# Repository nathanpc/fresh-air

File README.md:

# Fresh Air

The project used for [Nathan Campos](https://nathancampos.me/)'s video mapping
semester that was adapted to give a workshop on how to properly setup a Unity
interactive animation to work with a multi-layered video mapping projection.

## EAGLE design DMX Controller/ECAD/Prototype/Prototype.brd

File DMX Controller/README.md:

# MintyDMX

A tiny DMX controller that fits neatly inside an Altoids tin.

## License

<br />This work is licensed under a <a rel="license" href="http://creativecommons.org/licenses/by-nc-sa/4.0/">Creative Commons Attribution-NonCommercial-ShareAlike 4.0 International License</a>.

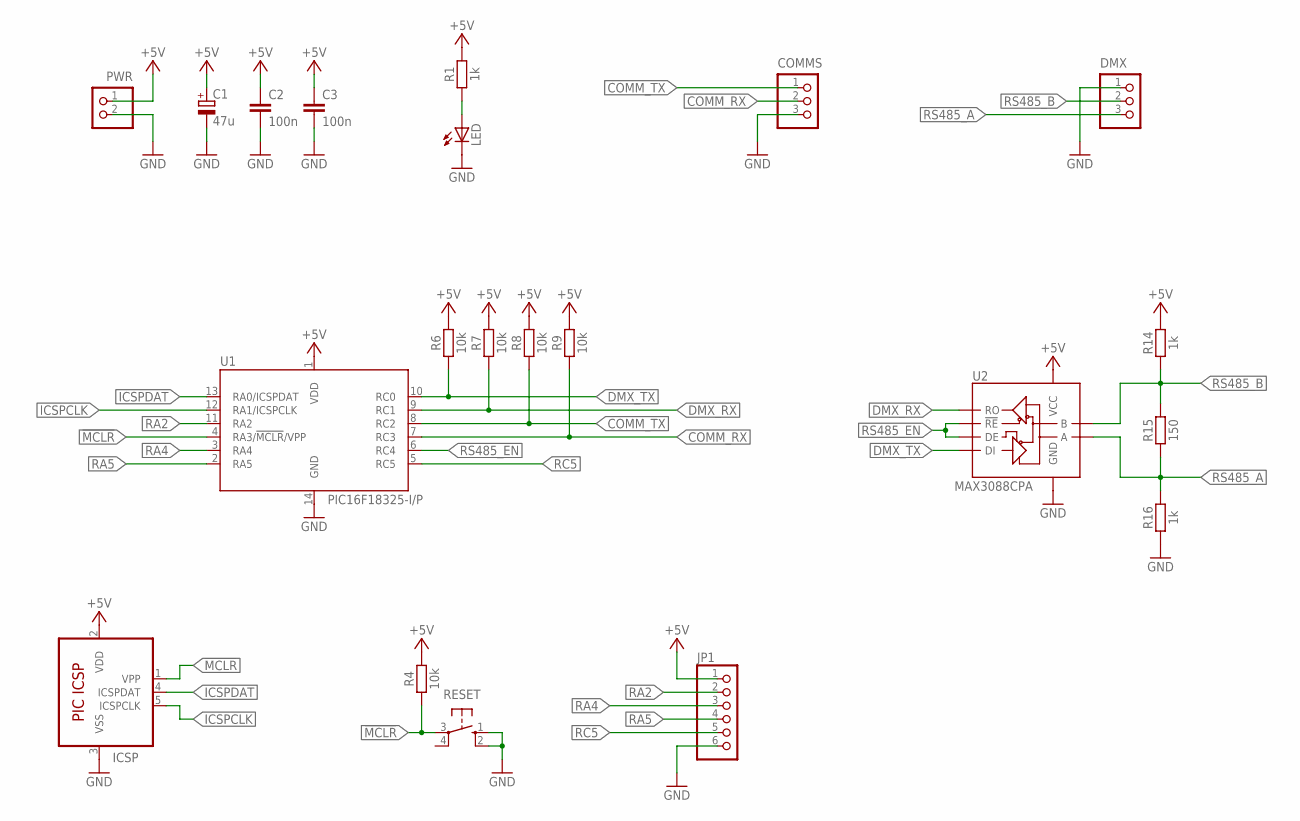
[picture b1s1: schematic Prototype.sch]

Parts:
C1: 47u; E2,5-6
C2, C3: 100n; C050-025X075
COMMS: B3B-XH-A
DMX: B3B-XH-A
ICSP: PIC-ICSP-XH6; B6B-XH-A
JP1: PINHD-1X6; 1X06
LED: LED-JST-XH; B2B-XH-A
PWR: B2B-XH-A
R1, R14, R16: 1k; 0207/10
R4, R6, R7, R8, R9: 10k; 0207/10
R15: 150; 0207/10
RESET: TACT-4PIN-THT; B3F-10XX
U1: PIC16F18325-I/P; DIL14
U2: MAX3088CPA; DIP-8

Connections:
!MCLR: ICSP.1 (VPP), R4.1, RESET.3, U1.4 (RA3/!MCLR!/VPP)
+5V: C1.+, C2.1, C3.1, ICSP.2 (VDD), JP1.1, PWR.1, R1.2, R4.2, R6.2, R7.2, R8.2, R9.2, R14.2, U1.1 (VDD), U2.8 (VCC)
COMM_RX: COMMS.2, R9.1, U1.7 (RC3)
COMM_TX: COMMS.1, R8.1, U1.8 (RC2)
DMX_RX: R7.1, U1.9 (RC1), U2.1 (RO)
DMX_TX: R6.1, U1.10 (RC0), U2.4 (DI)
GND: C1.-, C2.2, C3.2, COMMS.3, DMX.1, ICSP.3 (VSS), JP1.6, LED.2 (C), PWR.2, R16.1, RESET.1 (S), RESET.2 (S1), U1.14 (GND), U2.5 (GND)
ICSPCLK: ICSP.5 (ICSPCLK), U1.12 (RA1/ICSPCLK)
ICSPDAT: ICSP.4 (ICSPDAT), U1.13 (RA0/ICSPDAT)
unnamed: LED.1 (A), R1.1
RA2: JP1.2, U1.11 (RA2)
RA4: JP1.3, U1.3 (RA4)
RA5: JP1.4, U1.2 (RA5)
RC5: JP1.5, U1.5 (RC5)
RS485_A: DMX.3, R15.1, R16.2, U2.6 (A)
RS485_B: DMX.2, R14.1, R15.2, U2.7 (B)
RS485_EN: U1.6 (RC4), U2.2 (!RE), U2.3 (DE)

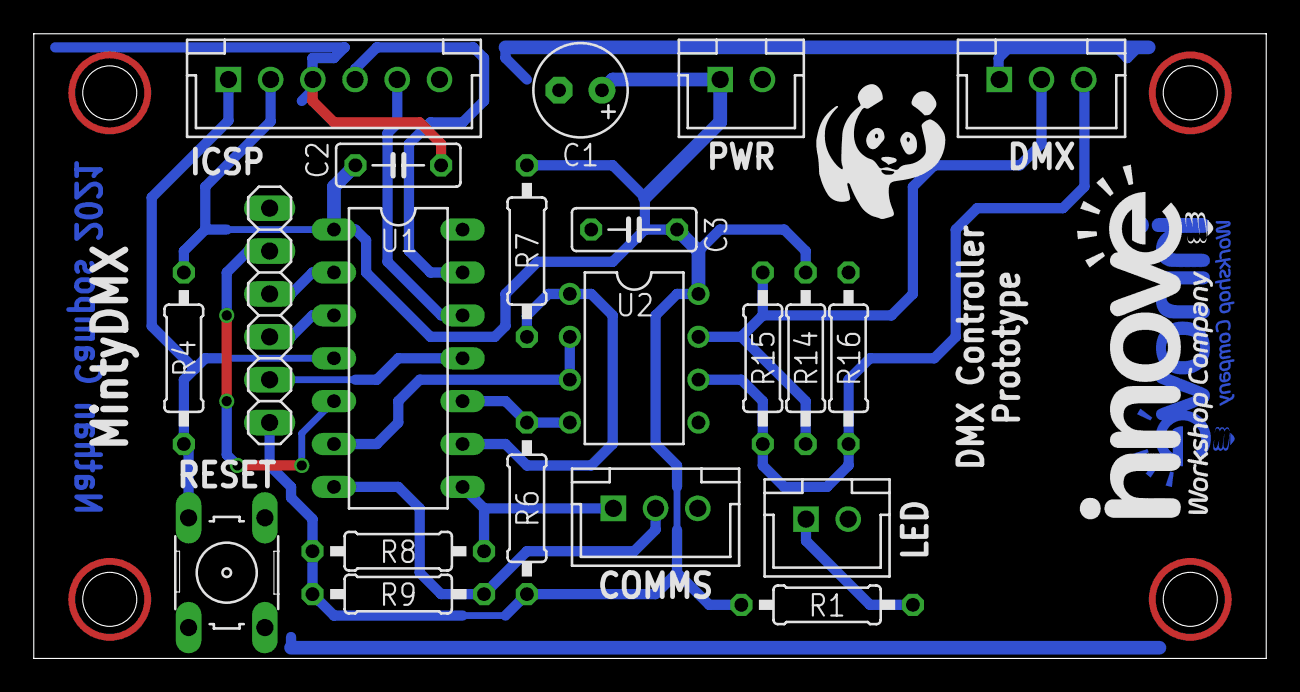
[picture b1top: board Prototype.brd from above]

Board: 2 copper layers, 73.0 x 37.0 mm, 21 parts (0 on the bottom side), 17 nets.

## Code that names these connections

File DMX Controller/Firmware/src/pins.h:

/* 
 * pins.h
 * Pin definitions.
 * 
 * @author Nathan Campos <nathan@innoveworkshop.com>
 */

#ifndef PINS_H
#define	PINS_H

//               16F18325
//             +----------+
// ICSP Data  -|RA0    RC0|- DMX Transmitter
// ICSP Clock -|RA1    RC1|- DMX Receiver
// Aux 1      -|RA2    RC2|- UART Transmitter
// Reset      -|RA3    RC3|- UART Receiver
// Aux 2      -|RA4    RC4|- DMX TX Enable
// Aux 3      -|RA5    RC5|- Aux 4
//             +----------+


// Pin definitions.
#define AUX_1     (1 << 2)  // RA2
#define AUX_2     (1 << 4)  // RA4
#define AUX_3     (1 << 5)  // RA5
#define DMX_TX    1         // RC0
#define DMX_RX    (1 << 1)  // RC1
#define UART_TX   (1 << 2)  // RC2
#define UART_RX   (1 << 3)  // RC3
#define DMX_TX_EN (1 << 4)  // RC4
#define AUX_4     (1 << 5)  // RC5

#endif	/* PINS_H */

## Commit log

2021-04-20 Empty Unity project
2021-04-29 Added paid scenary models
2021-04-29 inicial changes
2021-04-30 Basis for path following
2021-04-30 Movement proof-of-concept done
2021-04-30 Organized the code of the PathFollower script
2021-04-30 Modified the PathFollower script so that it's attached to characters instead of a waypoint container
2021-05-02 LMHPOLY assets
2021-05-02 Terrain
2021-05-02 terrain color
2021-05-02 rocks
2021-05-10 Removed the SampleScene
2021-05-10 Played around with a giant ball to simulate the fog effect
2021-05-10 Created all of the basic scripts to handle the movement interaction
2021-05-10 Tested the simple keyboard interaction using the keybaord
2021-05-10 Added support for an object to be controlled from the microphone hub adapter
2021-05-13 Improved the serial buffer parsing
2021-05-13 Joined the path follower with the microphone controller tests
2021-05-13 Added the ability to restart the path following
2021-05-24 missing color / sky
2021-05-24 scenary
2021-05-24 Added a way for the path follower script to stop for a while at some point
2021-05-24 Organized the scripts
2021-05-24 Started working on the prototype scene
2021-05-24 Enabled waypoints to change the object's rotation
2021-05-24 Added the fog to the prototype scene
2021-05-25 Fixed a variable name in WaypointStop
2021-05-25 Added scripts to handle the transformations
2021-05-25 Playing around with transformations
2021-05-25 Removed the unused collider script
2021-05-25 Added a simple function to debug unassigned references in the Inspector
2021-05-25 Added the ability for a waypoint to make the character jump
2021-05-26 2nd del scenary
2021-05-26 Imported the terrain changes and organized the scene
2021-05-26 Moved the terrain development scene
2021-05-26 Organized the project directory
2021-05-26 Put all of the characters in the scene and defined all of their waypoints
2021-05-26 Moving the fog after its animation has finished
2021-05-26 Fixed the transformation radius problems
2021-05-26 Added the ability to speed up and slow down the whole animation
2021-05-26 Finished all of the camera positions
2021-05-26 Added a script to change the material of a tree
2021-05-26 Changing the materials of Tree05
2021-05-26 Created and organized the tree materials
2021-05-26 Set all of the transform materials for the trees
2021-05-26 Populated the isolated terrain a bit
2021-05-26 Added the Main Scene to the build settings
2021-05-27 Minor change to the way the microphone controller is polled
2021-05-27 Added the Arduino source code that I forgot to put in
2021-06-21 new scenary
2021-06-23 Added Design students models
2021-06-23 Improved the interaction scripts just a bit
2021-06-23 Created the basis for the DMX stuff
2021-06-23 Organized all of the serial port scripts into their own folder
2021-06-23 Created a simple class just to provide baud rates to make it easier for people to use the DMX library
2021-06-23 Finished implementing the DMX spotlight
2021-06-23 Fully implemented the DMX robot light
2021-06-25 scenary & characters
2021-06-25 Implemented the fog machine interaction
2021-06-25 Improved the serial communication
2021-06-25 Started working on mapping things
2021-06-26 Implemented the new waypoint system and integrated animations
2021-06-26 Renamed the script testing scene
2021-06-26 Added the new scenery back
2021-06-26 Fixed the animations and waypoints
2021-06-26 Organized the workspace
2021-06-26 Organized everything and prepared the scene for waypoints
2021-06-27 Fixed the rotation of characters when using the waypoint rotation
2021-06-27 ccameras & waypoints
    camera waypoints fix:
    +- 2x entre o 1 waypoint e o 6
    rotaçao mais lenta entre waypoint 5 e 6
    segurar a camera no waypoint 6
2021-06-27 Implemented the fog shader
2021-06-27 Renamed the old scene
2021-06-27 Built a shader to transform textures
2021-06-27 Added a script to control the transformation shader
2021-06-27 Added a way to control the speed of movement between waypoints and fixed some of the waypoints
2021-06-30 Finished the project way late at night (6am) so here's huge dump of all the changes
2021-10-14 Stuff that was changed for the recording last semester
2022-06-05 Removed non-Unity, hardware-related, stuff
2022-06-05 Updated the README
2022-06-05 Updated the Unity version
2022-06-05 Cleaned up the project
2022-06-05 Finished setting up the entire mapping scene
2022-10-06 Very bad hack to bypass the DMX lighting controller
2022-10-07 More of the horrible hack to bypass DMX
